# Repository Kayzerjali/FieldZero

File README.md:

# FieldZero — Magnetic Field Cancellation for OPM MEG

System to reduce the residual magnetic field inside the QUBIC lab's mu-metal shielded enclosure, allowing the QuSpin QZFM sensors to zero and lock reliably.

See `docs/context.md` for full project context.

## Status

In development — lab access pending.

## Repository layout

```
docs/                 Project documentation (grows as work progresses)
data/
  raw/                Unmodified instrument output (write-once)
  processed/          Script outputs only — never hand-edit
Hardware/             KiCad — coil-driver PCB (see Hardware/Low_Current_Driver/)
  Common/             Shared symbol/footprint libraries
Software/             Python acquisition/analysis tooling
  src/fieldzero/      Python package
  scripts/
    characterisation/ Field measurement and analysis
    coil_cal/         Coil sensitivity calibration
    nulling/          Nulling procedure support
    figures/          All figure generation
  tests/
```

The Python setup and commands below are run from inside `Software/`.

## Setup

Python 3.11+. A venv is created per machine — **do not copy `.venv` between
machines**, it hardcodes absolute paths and platform-specific wheels. Recreate it
instead; it takes about a minute.

```powershell
py -m venv .venv
.venv\Scripts\activate
pip install -e ".[daq,dev]"
```

`[daq]` pulls in `nidaqmx`. Drop it on a machine with no card — `--mock` needs
nothing else. Drop `dev` if you are not running the tests. The NI-DAQmx driver
itself is a separate install from National Instruments and is not a pip package.

### Installing on a machine with no internet

Instrument PCs are often locked down. Build a wheelhouse **before** you go, on a
machine that does have network:

```powershell
.venv\Scripts\python.exe -m pip download -d wheels numpy scipy fastapi "uvicorn[standard]" nidaqmx
```

Copy `wheels/` across with the repo, then on the lab machine:

```powershell
py -m venv .venv
.venv\Scripts\activate
pip install --no-index --find-links wheels -e ".[daq]"
```

The front end needs no network either — uPlot is vendored into
`src/fieldzero/viewer/static/vendor/` rather than loaded from a CDN.

## Live viewer

```bash
python -m fieldzero.viewer            # against the NI-DAQ
python -m fieldzero.viewer --mock     # no hardware required
```

Opens a browser at `http://127.0.0.1:8000`. Split any pane left/right or
top/bottom and choose what goes in it: time domain, frequency domain (amplitude
or ASD), or phase (any channel against any other, with Pearson r and fitted
slope). The stats table below the panes gives per-channel mean and standard
deviation, and flags any channel sitting at the input rail.

Layouts persist across reloads and can be saved to / loaded from JSON.

Run `scripts/characterisation/verify_acquisition.py [--mock]` on arrival at the
lab to confirm the DAQ is reading every channel before starting a measurement.

The viewer binds to loopback, so a Windows firewall prompt on first run can be
declined. Use `--host 0.0.0.0` to watch from a laptop while the DAQ machine sits
in the shielded room — that one does need the firewall exception.

## Fallback scope

A plain matplotlib window. No server, no browser, no socket — a timer reads the
ring buffer in-process, so there is nothing between acquisition and the screen
that can stall, congest or time out. Use it if the browser viewer feels sluggish
on a given machine, or when you just want a scope up in one command.

It runs the same reducers as the browser viewer, so the DSP is identical: the
same windowing, the same ASD scaling, the same volts-based rail check, the same
correlation maths. Only the drawing differs.

### Running it

```bash
python -m fieldzero.scope                # against the NI-DAQ
python -m fieldzero.scope --mock         # no hardware required
```

With no `--pane`, you get one time-domain plot of all six channels. Close the
window to stop it.

### Choosing what to plot

`--pane` takes `KIND` or `KIND:CH,CH,...` and is **repeatable** — each one adds a
plot, stacked top to bottom in the order you give them.

| kind | channels | shows |
|------|----------|-------|
| `time` | any number (default: all six) | rolling time trace, newest sample at t=0 |
| `spectrum` | any number (default: all six) | amplitude spectral density, log axis |
| `phase` | **exactly two** | first against second, with a least-squares fit |

Channel names are `S1-X`, `S1-Y`, `S1-Z`, `S2-X`, `S2-Y`, `S2-Z` — the same names
the stats table uses. Get one wrong and it tells you the valid ones and exits.

```bash
# one time plot of two channels, and their spectrum underneath
python -m fieldzero.scope --pane time:S1-X,S2-X --pane spectrum:S1-X,S2-X

# is sensor 2 seeing the same field as sensor 1?
python -m fieldzero.scope --pane phase:S1-X,S2-X

# what is the residual on the Z axis, in raw volts, over 10 seconds?
python -m fieldzero.scope --pane time:S1-Z,S2-Z --units V --window 10
```

### The other flags

| flag | default | what it does |
|------|---------|--------------|
| `--mock` | off | simulated source; no DAQ needed |
| `--window N` | `5` | seconds of history each pane shows |
| `--units pT\|V` | `pT` | display units. **Volts are ground truth** — the V/nT figure is unverified |
| `--fps N` | `10` | redraw rate. Drop it to `5` on a slow machine |
| `--sample-rate N` | `1000` | samples/second per channel. Startup only |

### Reading the window

The red or grey strip along the top is the readout, updated twice a second:

- Normally it lists every channel's mean ± standard deviation in the chosen units.
- If **any channel is at the input rail** it turns red and says so, and it says
  nothing else. That warning takes priority because a clipped channel still
  reports a mean that looks like a perfectly reasonable field value. When you see
  it, the true field on that channel is larger than ±5 V can represent, and every
  number from it is fiction.

A phase pane also prints its Pearson *r* and fitted slope into that strip: *r*
near 1 means both channels are seeing the same field, and the slope is the gain
ratio between them.

### What you give up

Panes are fixed at launch. There is no clicking, no splitting, no changing
channels while it runs — to change the layout, close it and relaunch with
different `--pane` flags. That is the trade for having nothing that can go wrong.

### If you edit `scope.py`

Rendering uses blitting, and has to. A full matplotlib redraw of three panes
costs ~120 ms (~8 fps), and the cost is the redraw itself — thinning the data does
not help. Blitting the traces over a cached background costs ~20 ms instead. Two
consequences are load-bearing:

- **A pane's axes contain traces and nothing else.** Rasterising text costs more
  per frame than every trace in every pane put together (~27 ms vs ~22 ms), which
  is why all text lives in the status strip — it has its own bbox, so it can be
  redrawn at 2 Hz independently — and why legends and titles sit *above* the axes,
  outside the blitted region, where they survive in the cached background for free.
- **Axis limits use hysteresis.** They only move when the data leaves them, because
  a rescale forces a full redraw. Rescaling every frame would throw away
  everything blitting buys. `test_scope.py` asserts steady state needs none.

## Acquisition notes

Sample rate is a **startup** parameter (`--sample-rate`, default 1000 Hz), not a
runtime one: changing it means rebuilding the DAQ task, and doing that mid-run is
what made the previous project's axis switching unreliable. The task is opened
once over all six channels and never reconfigured; selecting an axis is purely a
display concern.

Acquisition yields **volts**. The V/nT conversion is applied at display time
(see below) — so saturation is detected against the known input range rather
than an unverified sensitivity figure.

## Hardware

| Item | Status |
|------|--------|
| QuSpin QZFM sensors × 2 | In lab — gen TBD |
| Cancellation coils | Not yet installed |
| Current source | TBD |
| NI-DAQ (Dev1, ai0–ai5) | In lab — model TBD, confirm in NI MAX |

Three acquisition settings in `src/fieldzero/config.py` need confirming against
the actual card. MEG_DSP never set them, so it silently ran on the `nidaqmx`
defaults:

| Setting | Value | Why it matters |
|---------|-------|----------------|
| `voltage_range` | ±5 V | Where a channel clips. This is the `nidaqmx` default, never a decision. At the inherited 2.7 V/nT that is a clip at ~1.85 nT — and the residual field is believed to be nT-scale, so channels may already be railing. |
| `terminal_config` | RSE | RSE vs differential materially changes the noise floor. |
| `sensitivity_v_per_nT` | 2.7 | **Unverified** — inherited from MEG_DSP, and the QZFM generation is still unconfirmed. Volts are ground truth until this is checked against the sensor label. |

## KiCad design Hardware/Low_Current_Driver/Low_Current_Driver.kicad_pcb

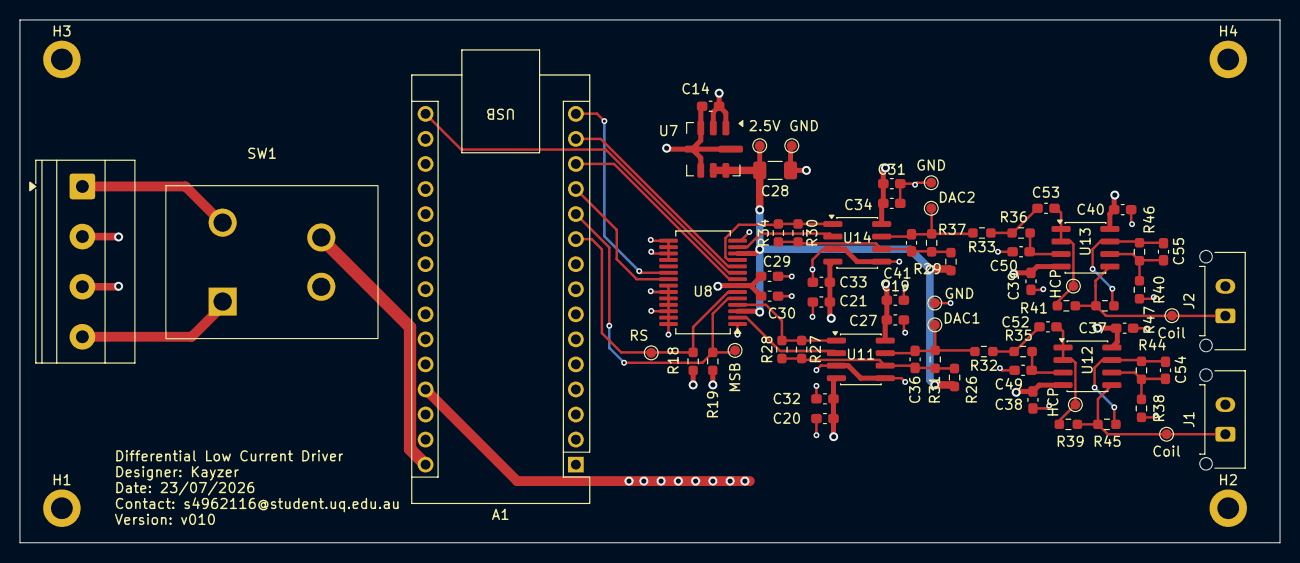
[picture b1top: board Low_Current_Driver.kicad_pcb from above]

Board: 4 copper layers, 127.8 x 53.0 mm, 73 parts (0 on the bottom side), 34 nets.

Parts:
2.5V: TestPoint_Probe; TestPoint_Pad_D1.0mm
A1: Arduino_Nano_R4; Arduino_Nano
C14, C19, C20, C21, C30, C31, C36, C37, C38, C39, C40, C41: 100n; C_0603_1608Metric_Pad1.08x0.95mm_HandSolder
C27, C32, C33, C34, C49, C50, C52, C53: 1u; C_0603_1608Metric_Pad1.08x0.95mm_HandSolder
C28: 10u; C_1206_3216Metric_Pad1.33x1.80mm_HandSolder
C29: 10n; C_0603_1608Metric_Pad1.08x0.95mm_HandSolder
C54, C55: 4.7u; C_0603_1608Metric_Pad1.08x0.95mm_HandSolder
Coil: TestPoint_Probe; TestPoint_Pad_D1.0mm
Coil#2: TestPoint_Probe; TestPoint_Pad_D1.0mm
DAC1, DAC2: TestPoint_Probe; TestPoint_Pad_D1.0mm
GND: TestPoint_Probe; TestPoint_Pad_D1.0mm
GND#2, GND#3: TestPoint_Probe; TestPoint_Pad_D1.0mm
H1, H2, H3, H4: MountingHole_Pad; MountingHole_2.2mm_M2_DIN965_Pad
HCP: TestPoint_Probe; TestPoint_Pad_D1.0mm
HCP#2: TestPoint_Probe; TestPoint_Pad_D1.0mm
J1, J2: Conn_01x02_Socket; Molex_Micro-Fit_3.0_43650-0215_1x02_P3.00mm_Vertical
J3: Screw_Terminal_01x04; TerminalBlock_Phoenix_MKDS-1,5-4-5.08_1x04_P5.08mm_Horizont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
MSB: TestPoint_Probe; TestPoint_Pad_D1.0mm
R18, R19, R26, R27, R28, R29, R30, R31, R34, R37: 10k; R_0603_1608Metric_Pad0.98x0.95mm_HandSolder
R32, R33, R35, R36: 1k; R_0603_1608Metric_Pad0.98x0.95mm_HandSolder
R38, R39, R40, R41, R44, R45, R46, R47: 249; R_0603_1608Metric_Pad0.98x0.95mm_HandSolder
RS: TestPoint_Probe; TestPoint_Pad_D1.0mm
SW1: SW_DPST; DPST_RA83231100
U7: LTC6655-2.5; Analog_LCC-8_5x5mm_P1.27mm
U8: DAC8814; SSOP-28_5.3x10.2mm_P0.65mm
U11, U12, U13, U14: OPA2210; SOIC-8_3.9x4.9mm_P1.27mm

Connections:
+5VD: A1.27 (+5V), C14.1, C29.1, C30.1, R18.2, R19.2, U7.1 (~SHDN), U7.2 (Vin), U8.7 (VDD)
+9V: A1.30 (VIN), C19.1, C27.1, C31.1, C34.1, C37.1, C40.1, SW1.4, U11.8 (V+), U12.8 (V+), U13.8 (V+), U14.8 (V+)
-9V: C20.1, C21.1, C32.1, C33.1, C38.2, C39.2, SW1.2, U11.4 (V-), U12.4 (V-), U13.4 (V-), U14.4 (V-)
/Coil_Drive_A/HCP_FB: C54.2, R38.1, R44.2, U12.6 (-)
/Coil_Drive_A/HCP_Out: C54.1, R44.1, R45.1, U12.7
/Coil_Drive_A/Iin_coil: Coil.1 (1_1), J1.1, R39.1, R45.2, U12.5 (+)
/Coil_Drive_A/Vout_dac: C36.2, DAC1.1 (1_1), R31.2, R32.2, U11.7
/Coil_Drive_B/HCP_FB: C55.2, R40.1, R46.2, U13.6 (-)
/Coil_Drive_B/HCP_Out: C55.1, R46.1, R47.1, U13.7
/Coil_Drive_B/Iin_coil: Coil#2.1 (1_1), J2.1, R41.1, R47.2, U13.5 (+)
/Coil_Drive_B/Vout_dac: C41.2, DAC2.1 (1_1), R33.2, R37.2, U14.7
/DAC/CLK: A1.16 (SCK), U8.9 (CLK)
/DAC/DAC_Buffer_A/Iin: U8.2 (Iout_A), U11.2 (-)
/DAC/DAC_Buffer_A/Rfb: R27.1, R28.1, U8.4 (Rfb_A), U11.1
/DAC/DAC_Buffer_B/Iin: U8.13 (Iout_B), U14.2 (-)
/DAC/DAC_Buffer_B/Rfb: R30.1, R34.1, U8.11 (Rfb_B), U14.1
/DAC/MSB: A1.11 (D8), MSB.1 (1_1), R19.1, U8.5 (MSB)
/DAC/SDI: A1.14 (MOSI), U8.10 (SDI)
/DAC/SDO: A1.15 (MISO), U8.20 (SDO)
/DAC/Vref_2.5V: 2.5V.1 (1_1), C28.1, R26.1, R29.1, U7.6 (Vout_S), U7.7 (Vout_F), U8.3 (VREF_A), U8.12 (VREF_B)
/DAC/~CS: A1.13 (D10), U8.8 (~CS)
/DAC/~LDAC: A1.12 (D9), U8.21 (~LDAC)
/DAC/~RS: A1.10 (D7), R18.1, RS.1 (1_1), U8.6 (~RS)
GND: A1.4 (GND), A1.29 (GND), C14.2, C19.2, C20.2, C21.2, C27.2, C28.2, C29.2, C30.2, C31.2, C32.2, C33.2, C34.2, C37.2, C38.1, C39.1, C40.2, C49.2, C50.2, GND.1 (1_1), GND#2.1 (1_1), GND#3.1 (1_1), H1.1 (1_1), H2.1 (1_1), H3.1 (1_1), H4.1 (1_1), J1.2, J2.2, J3.2, J3.3, R38.2, R40.2, U7.3 (GND), U7.4 (GND), U7.5 (GND), U7.8 (GND), U8.1 (AGND_A), U8.14 (AGND_B), U8.15 (AGND_C), U8.16 (Iout_C), U8.17 (VREF_C), U8.18 (Rfb_C), U8.22 (AGND_F), U8.23 (VSS), U8.24 (DGND), U8.25 (Rfb_D), U8.26 (VREF_D), U8.27 (Iout_D), U8.28 (AGND_D), U11.3 (+), U11.5 (+), U14.3 (+), U14.5 (+)
unnamed: C52.2, R32.1, R35.2
unnamed: C53.2, R33.1, R36.2
unnamed: J3.1, SW1.3
unnamed: J3.4, SW1.1
unnamed: C36.1, R26.2, R27.2, R28.2, R31.1, U11.6 (-)
unnamed: C49.1, R35.1, U12.3 (+)
unnamed: C52.1, HCP.1 (1_1), R39.2, U12.1, U12.2 (-)
unnamed: C50.1, R36.1, U13.3 (+)
unnamed: C53.1, HCP#2.1 (1_1), R41.2, U13.1, U13.2 (-)
unnamed: C41.1, R29.2, R30.2, R34.2, R37.1, U14.6 (-)

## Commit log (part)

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2026-06-27 readme modified to exclude conda env usage
